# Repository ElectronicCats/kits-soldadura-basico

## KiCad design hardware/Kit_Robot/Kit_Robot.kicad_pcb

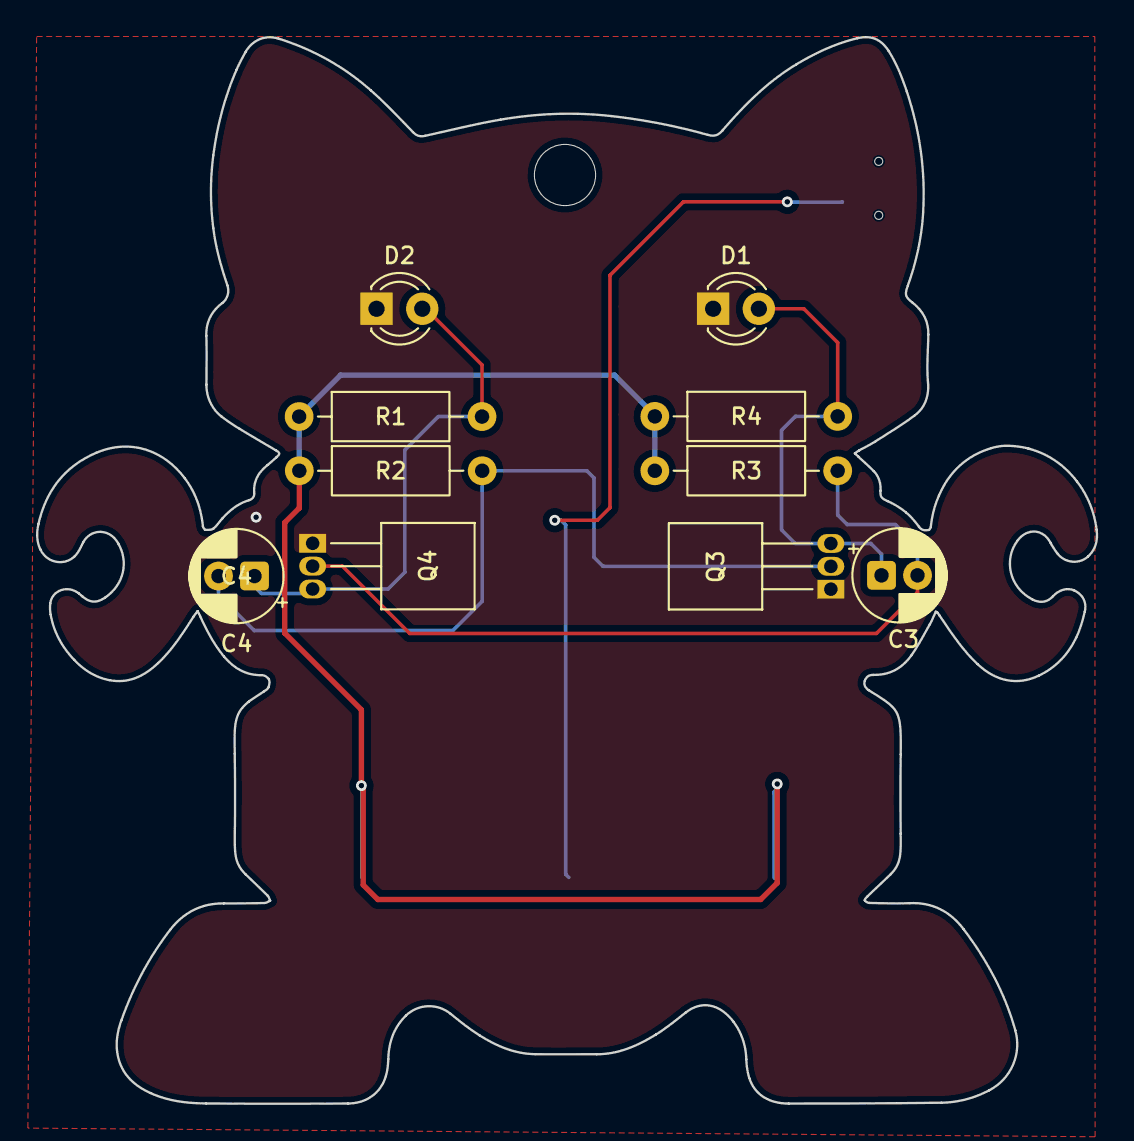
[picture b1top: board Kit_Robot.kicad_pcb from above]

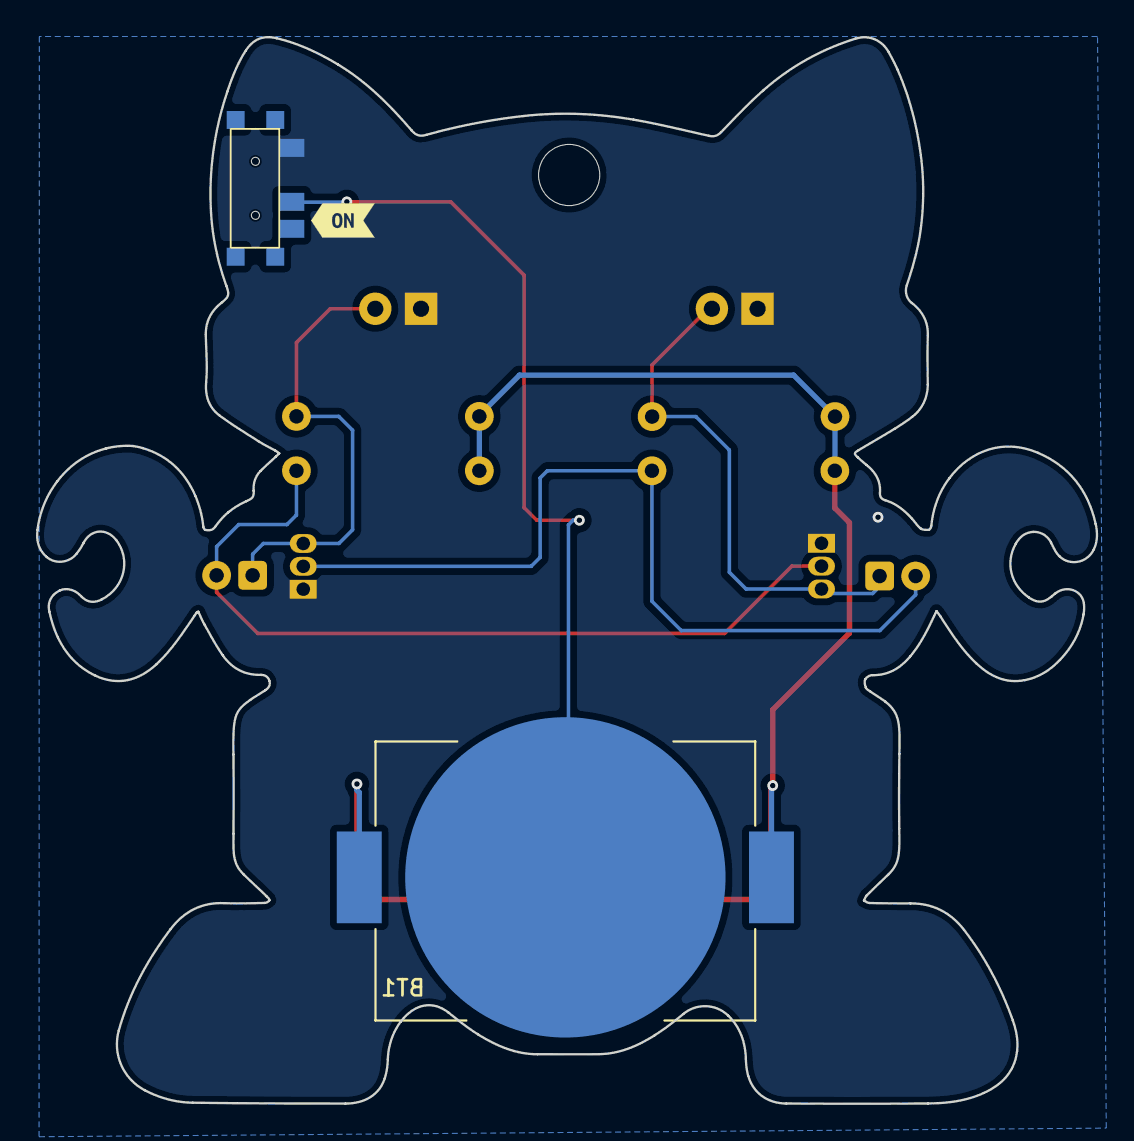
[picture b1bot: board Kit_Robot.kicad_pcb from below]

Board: 2 copper layers, 58.9 x 59.3 mm, 13 parts (3 on the bottom side), 7 nets.

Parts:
BT1: Battery_Cell; BAT_BAT-HLD-001
C3, C4: 10uF; CP_Radial_D5.0mm_P2.00mm
D1, D2: BLUE; LED_D3.0mm
Q3, Q4: BC548; TO-92_Inline_Horizontal2
R1, R4: 330R; R_Axial_DIN0207_L6.3mm_D2.5mm_P10.16mm_Horizontal
R2, R3: 100K; R_Axial_DIN0207_L6.3mm_D2.5mm_P10.16mm_Horizontal
SW2: On; SW-SMD_3P-P1.50_L2.7-W6.6
kibuzzard-6AC42980: G***; kibuzzard-6AC42980

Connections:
+3.3V: BT1.2 (+), R1.1, R2.1, R3.1, R4.1
GND: D1.1 (K), D2.1 (K), Q3.1 (E), Q4.1 (E), SW2.1 (A)
unnamed: BT1.1 (-), SW2.2 (B)
unnamed: C3.1, D1.2 (A), Q3.3 (C), R4.2
unnamed: C4.1, D2.2 (A), Q4.3 (C), R1.2
unnamed: C4.2, Q3.2 (B), R2.2
unnamed: C3.2, Q4.2 (B), R3.2

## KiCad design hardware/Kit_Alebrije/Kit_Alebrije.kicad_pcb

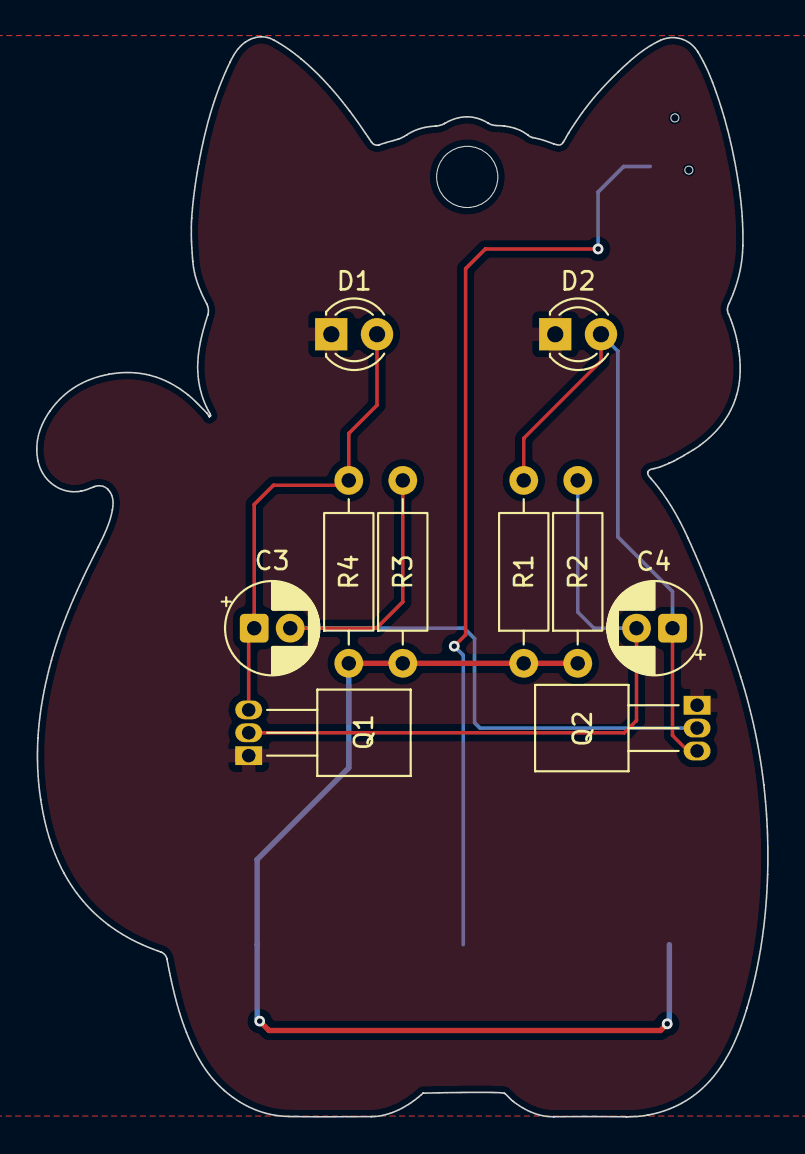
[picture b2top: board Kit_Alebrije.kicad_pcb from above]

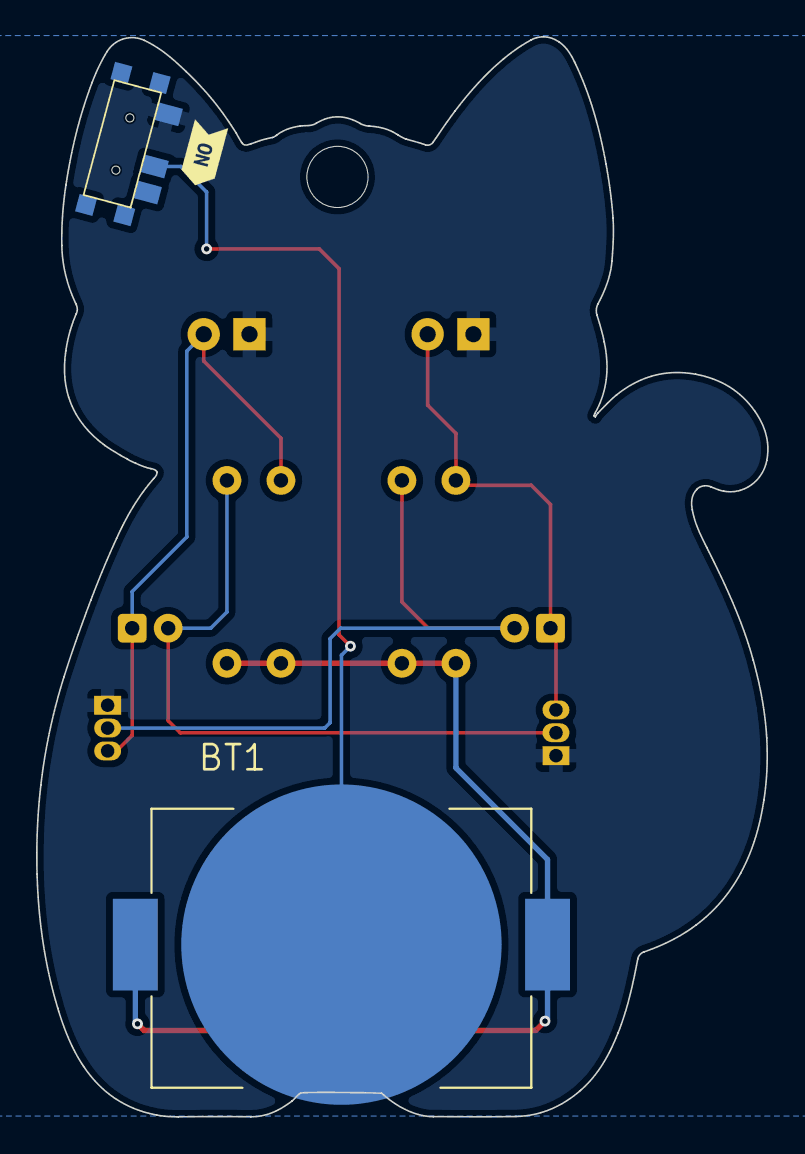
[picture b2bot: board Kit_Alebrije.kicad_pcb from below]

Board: 2 copper layers, 40.6 x 60.0 mm, 13 parts (3 on the bottom side), 7 nets.

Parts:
BT1: Battery_Cell; BAT_BAT-HLD-001
C3, C4: 10uF; CP_Radial_D5.0mm_P2.00mm
D1, D2: BLUE; LED_D3.0mm
Q1, Q2: BC547; TO-92_Inline_Horizontal1
R1, R4: 330R; R_Axial_DIN0207_L6.3mm_D2.5mm_P10.16mm_Horizontal
R2, R3: 100K; R_Axial_DIN0207_L6.3mm_D2.5mm_P10.16mm_Horizontal
SW2: On; SW-SMD_3P-P1.50_L2.7-W6.6
kibuzzard-6AC559DE: G***; kibuzzard-6AC559DE

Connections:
+3.3V: BT1.2 (+), R1.1, R2.1, R3.1, R4.1
GND: D1.1 (K), D2.1 (K), Q1.1 (E), Q2.1 (E), SW2.1 (A)
unnamed: BT1.1 (-), SW2.2 (B)
unnamed: C3.1, D1.2 (A), Q1.3 (C), R4.2
unnamed: C4.1, D2.2 (A), Q2.3 (C), R1.2
unnamed: C4.2, Q1.2 (B), R2.2
unnamed: C3.2, Q2.2 (B), R3.2
